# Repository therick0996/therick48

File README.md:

# therick48

A 4x12 ortho keyboard with USB C, SMD components, and 19mm spacing.

This is essentially a dumbed down Planck clone.

If you're looking for something with a numpad, look at the [therick48.16](https://github.com/dierickdie/therick48.16) or [therick48.16SP](https://github.com/dierickdie/therick48.16SP).

Although everything should<sup>(tm)</sup> work as is, it hasn't been physically tested.

**USE AT YOUR OWN RISK!!!** I am not responsible for any dumb things you do, fry your computer, break anything, etc.

## FAQ:
#### Does it have MIT/2x2u/etc.? 
No. Grid for life

#### Does it have backlighting?
No

#### Does it have RGB?
No

#### Does it have a rotary encoder?
No

#### Does it have hotswap?
No

#### Does it have Alps support?
No

#### Choc support?
No

#### Will you add any of these?
No

#### Why not?
I don't wanna

#### Will it fit a Planck case?
Yes! In theory. Hasn't been tested.

#### Why USB C?
That's a dumb question

#### Will you add micro/mini/any USB other than type C?
No

#### Why not?
USB C is the future. Until a new standard comes out

#### But I don't have any USB C cables.
Boo hoo. I suggest building one. Zap Cables is a good place to get parts

#### Why is it named therick48?
It started in fall of 2005 when I was just a boy. I started a new job, and needed a login name. The manager wrote The Rick (my first name is Rick). It has stuck ever since. Thanks, Sam! And 48 keys, but that was obvious. I hope.

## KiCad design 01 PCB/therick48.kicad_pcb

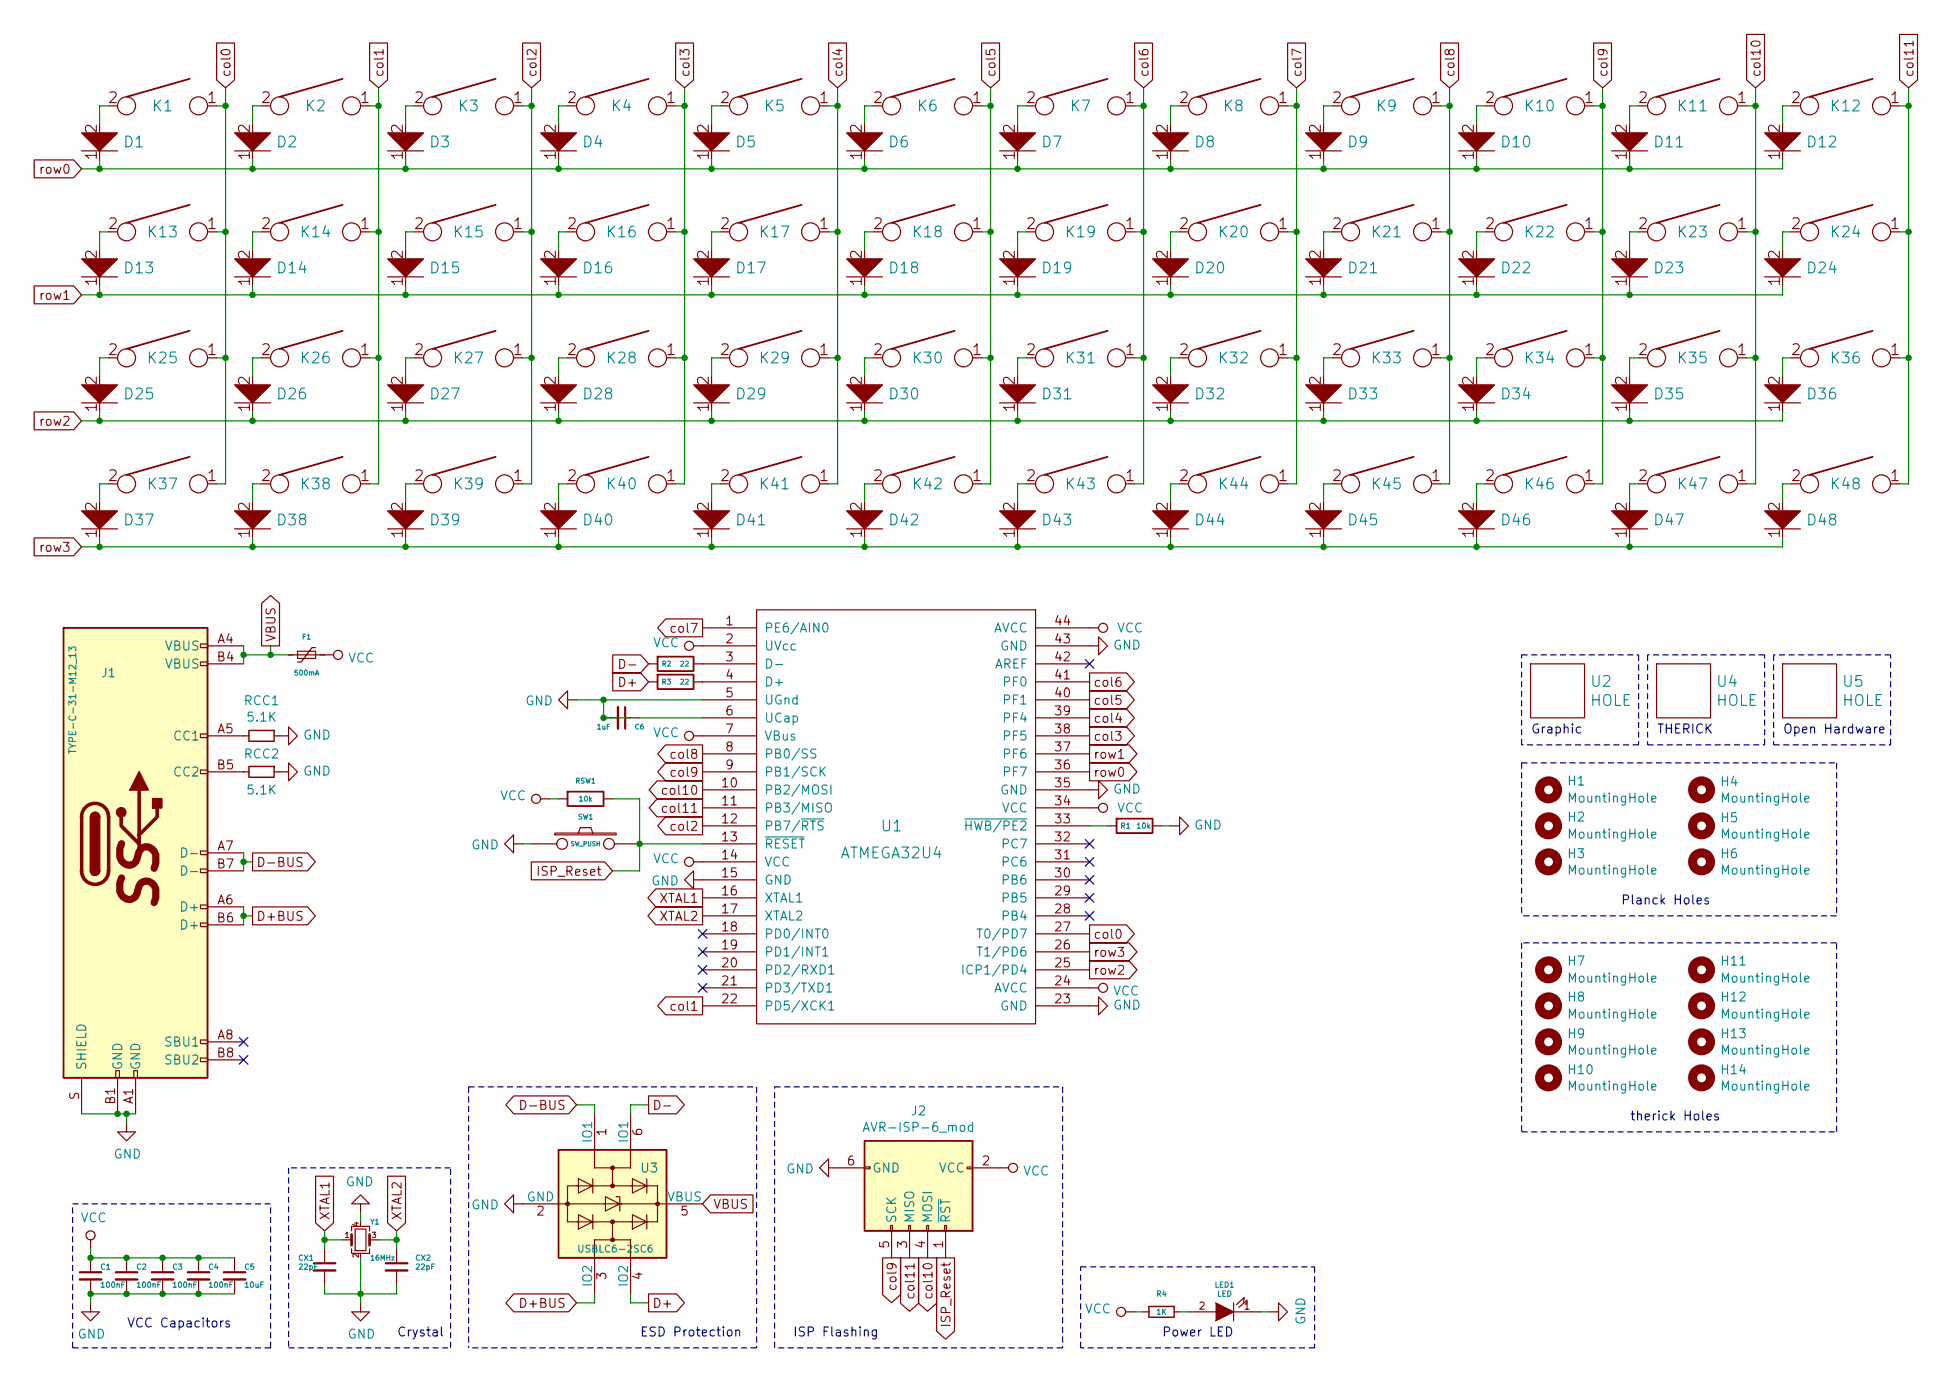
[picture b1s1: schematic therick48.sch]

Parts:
C1, C2, C3, C4: 100nF; C_0805_2012Metric_Pad1.15x1.40mm_HandSolder
C5: 10uF; C_0805_2012Metric_Pad1.15x1.40mm_HandSolder
C6: 1uF; C_0805_2012Metric_Pad1.15x1.40mm_HandSolder
CX1, CX2: 22pF; C_0805_2012Metric_Pad1.15x1.40mm_HandSolder
D1, D2, D3, D4, D5, D6, D7, D8, D9, D10, D11, D12, D13, D14, D15, D16, D17, D18, D19, D20, D21, D22, D23, D24, D25, D26, D27, D28, D29, D30, D31, D32, D33, D34, D35, D36, D37, D38, D39, D40, D41, D42, D43, D44, D45, D46, D47, D48: D; D_SOD-123_modified
F1: 500mA; Fuse_0805_2012Metric_Pad1.15x1.40mm_HandSolder
H1, H2, H3, H4, H5, H6, H7, H8, H9, H10, H11, H12, H13, H14: MountingHole; Generic-Mounthole
J1: TYPE-C-31-M12_13; TYPE-C-31-M-12
J2: AVR-ISP-6_mod; PIN_HEADER_1x6_OFFSET
K1, K2, K3, K4, K5, K6, K7, K8, K9, K10, K11, K12, K13, K14, K15, K16, K17, K18, K19, K20, K21, K22, K23, K24, K25, K26, K27, K28, K29, K30, K31, K32, K33, K34, K35, K36, K37, K38, K39, K40, K41, K42, K43, K44, K45, K46, K47, K48: KEYSW; MX100
LED1: LED; LED_0805_2012Metric_Pad1.15x1.40mm_HandSolder
R1: 10k; R_0805_2012Metric_Pad1.15x1.40mm_HandSolder
R2, R3: 22; R_0805_2012Metric_Pad1.15x1.40mm_HandSolder
R4: 1K; R_0805_2012Metric_Pad1.15x1.40mm_HandSolder
RCC1, RCC2: 5.1K; R_0805_2012Metric_Pad1.15x1.40mm_HandSolder
RSW1: 10k; R_0805_2012Metric_Pad1.15x1.40mm_HandSolder
SW1: SW_PUSH; SKQG-1155865
U1: ATMEGA32U4; ATMEGA32U4-AU
U2: HOLE; rick_large
U3: USBLC6-2SC6; SOT-23-6
U4: HOLE; THERICK
U5: HOLE; OSHW-Logo_11.4x12mm_SilkScreen
Y1: 16MHz; Crystal_SMD_3225-4Pin_3.2x2.5mm_HandSoldering

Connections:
D+: R3.2, U3.4 (IO2)
D+BUS: J1.A6 (D+), J1.B6 (D+), U3.3 (IO2)
D-: R2.2, U3.6 (IO1)
D-BUS: J1.A7 (D-), J1.B7 (D-), U3.1 (IO1)
GND: C1.2, C2.2, C3.2, C4.2, C5.2, C6.2, CX1.2, CX2.2, J1.A1 (GND), J1.B1 (GND), J1.S (SHIELD), J2.6 (GND), LED1.1 (K), R1.1, RCC1.1, RCC2.1, SW1.1, U1.5 (UGnd), U1.15 (GND), U1.23 (GND), U1.35 (GND), U1.43 (GND), U3.2 (GND), Y1.2, Y1.4
ISP_Reset: J2.1 (~RST), RSW1.1, SW1.2, U1.13 (~RESET)
unnamed: C6.1, U1.6 (UCap)
unnamed: D1.2, K1.2
unnamed: D2.2, K2.2
unnamed: D3.2, K3.2
unnamed: D4.2, K4.2
unnamed: D5.2, K5.2
unnamed: D6.2, K6.2
unnamed: D7.2, K7.2
unnamed: D8.2, K8.2
unnamed: D9.2, K9.2
unnamed: D10.2, K10.2
unnamed: D11.2, K11.2
unnamed: D12.2, K12.2
unnamed: D13.2, K13.2
unnamed: D14.2, K14.2
unnamed: D15.2, K15.2
unnamed: D16.2, K16.2
unnamed: D17.2, K17.2
unnamed: D18.2, K18.2
unnamed: D19.2, K19.2
unnamed: D20.2, K20.2
unnamed: D21.2, K21.2
unnamed: D22.2, K22.2
unnamed: D23.2, K23.2
unnamed: D24.2, K24.2
unnamed: D25.2, K25.2
unnamed: D26.2, K26.2
unnamed: D27.2, K27.2
unnamed: D28.2, K28.2
unnamed: D29.2, K29.2
unnamed: D30.2, K30.2
unnamed: D31.2, K31.2
unnamed: D32.2, K32.2
unnamed: D33.2, K33.2
unnamed: D34.2, K34.2
unnamed: D35.2, K35.2
unnamed: D36.2, K36.2
unnamed: D37.2, K37.2
unnamed: D38.2, K38.2
unnamed: D39.2, K39.2
unnamed: D40.2, K40.2
unnamed: D41.2, K41.2
unnamed: D42.2, K42.2
unnamed: D43.2, K43.2
unnamed: D44.2, K44.2
unnamed: D45.2, K45.2
unnamed: D46.2, K46.2
unnamed: D47.2, K47.2
unnamed: D48.2, K48.2
unnamed: J1.A5 (CC1), RCC1.2
unnamed: J1.B5 (CC2), RCC2.2
unnamed: LED1.2 (A), R4.1
unnamed: R1.2, U1.33 (~HWB/PE2)
unnamed: R2.1, U1.3 (D-)
unnamed: R3.1, U1.4 (D+)
VBUS: F1.2, J1.A4 (VBUS), J1.B4 (VBUS), U3.5 (VBUS)
VCC: C1.1, C2.1, C3.1, C4.1, C5.1, F1.1, J2.2 (VCC), R4.2, RSW1.2, U1.2 (UVcc), U1.7 (VBus), U1.14 (VCC), U1.24 (AVCC), U1.34 (VCC), U1.44 (AVCC)
XTAL1: CX1.1, U1.16 (XTAL1), Y1.1
XTAL2: CX2.1, U1.17 (XTAL2), Y1.3
col0: K1.1, K13.1, K25.1, K37.1, U1.27 (T0/PD7)
col1: K2.1, K14.1, K26.1, K38.1, U1.22 (PD5/XCK1)
col2: K3.1, K15.1, K27.1, K39.1, U1.12 (PB7/~RTS)
col3: K4.1, K16.1, K28.1, K40.1, U1.38 (PF5)
col4: K5.1, K17.1, K29.1, K41.1, U1.39 (PF4)
col5: K6.1, K18.1, K30.1, K42.1, U1.40 (PF1)
col6: K7.1, K19.1, K31.1, K43.1, U1.41 (PF0)
col7: K8.1, K20.1, K32.1, K44.1, U1.1 (PE6/AIN0)
col8: K9.1, K21.1, K33.1, K45.1, U1.8 (PB0/SS)
col9: J2.5 (SCK), K10.1, K22.1, K34.1, K46.1, U1.9 (PB1/SCK)
col10: J2.4 (MOSI), K11.1, K23.1, K35.1, K47.1, U1.10 (PB2/MOSI)
col11: J2.3 (MISO), K12.1, K24.1, K36.1, K48.1, U1.11 (PB3/MISO)
row0: D1.1, D2.1, D3.1, D4.1, D5.1, D6.1, D7.1, D8.1, D9.1, D10.1, D11.1, D12.1, U1.36 (PF7)
row1: D13.1, D14.1, D15.1, D16.1, D17.1, D18.1, D19.1, D20.1, D21.1, D22.1, D23.1, D24.1, U1.37 (PF6)
row2: D25.1, D26.1, D27.1, D28.1, D29.1, D30.1, D31.1, D32.1, D33.1, D34.1, D35.1, D36.1, U1.25 (ICP1/PD4)
row3: D37.1, D38.1, D39.1, D40.1, D41.1, D42.1, D43.1, D44.1, D45.1, D46.1, D47.1, D48.1, U1.26 (T1/PD6)

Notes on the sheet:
VCC Capacitors
Planck Holes
Graphic
Crystal
ESD Protection
ISP Flashing
therick Holes
THERICK
Open Hardware
Power LED

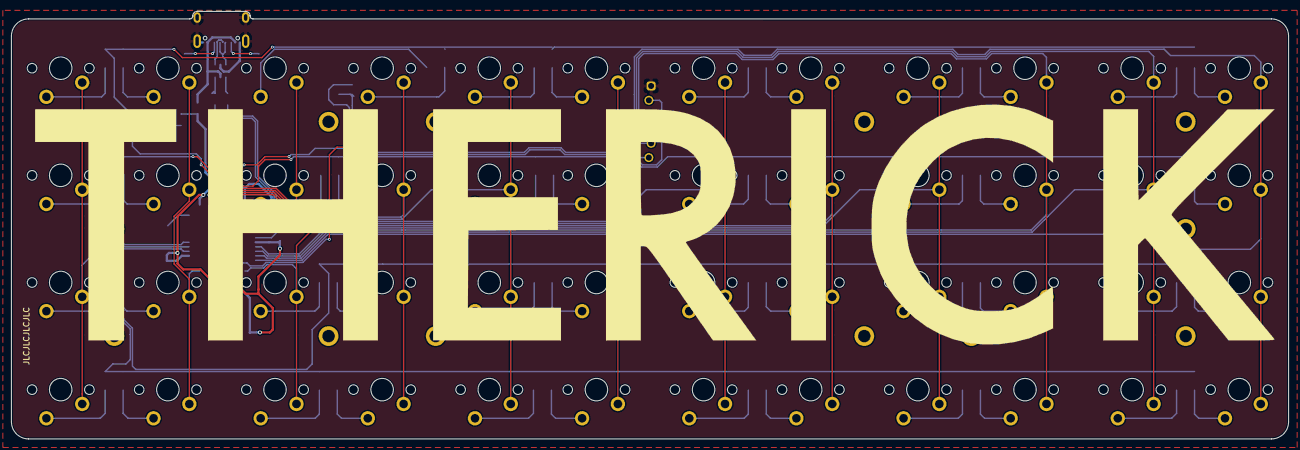
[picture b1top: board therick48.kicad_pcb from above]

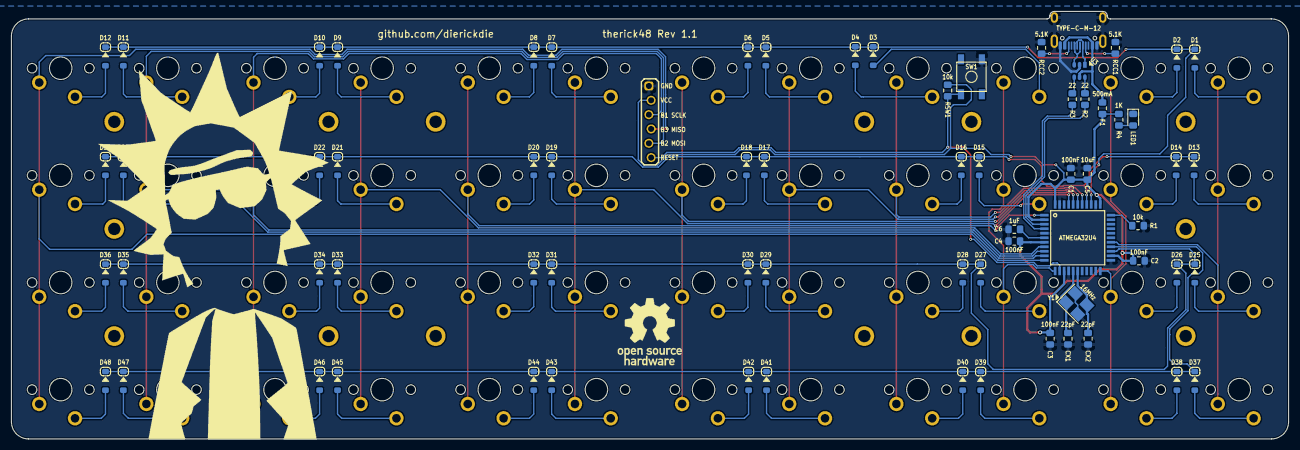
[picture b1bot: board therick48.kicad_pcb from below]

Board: 2 copper layers, 226.5 x 75.8 mm, 136 parts (73 on the bottom side), 81 nets.

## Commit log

2020-02-08 Initial Commit
    Was previously just 'therick' but renamed to therick48
2020-02-08 Align Switches
2020-02-21 Add Gerbers
2020-02-22 Update firmware
2020-02-23 Changed pins to make routing cleaner
2020-03-05 Final Gerbers
2020-03-12 Made capacitors effective
2020-03-16 Add reset hole to bottom plate
2020-03-18 Update keymap
2020-03-21 Updated mounting holes
2020-04-05 Updare keymapc.
2020-04-28 stupid .ds_store
2020-05-08 Added more mounting holes
2020-05-09 Move ISP Header
2020-05-09 New Gerbers
2020-05-10 Made ISP header actually work
2020-05-10 Aadd hex files
2020-05-14 Update Gerber files
2020-05-15 Update fp-info-cache
2020-05-16 Add reset hole
2020-05-17 Move mounting holes to PCB
2020-05-17 Update bottom plate
2020-05-23 Changed a trace
2020-05-24 Add v 1.0
2020-05-24 Rename folders
2020-05-24 Rename previos version folder
2020-05-25 Add power LED
2020-05-30 New Gerber files
2020-05-31 Gerber
2020-06-03 cache
2020-06-20 New gerber
2021-03-23 enable mouse clicks
2021-04-10 add combined keymap
2021-04-11 consolidated keymaps
